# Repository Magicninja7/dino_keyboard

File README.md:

# Description
A keyboard with 84 keys, a ssd1306 mini-display, and 2 ec11 potentiometers. It has a unque look, with lots of extra keys for ex. undo, copy, paste, print, etc. You can also control the brightness and volume with the knobs (yes, i change the brightness that often).
Why? i literally thought: hmm, a keyboard would look nice on my desk. And highway happened, so i actually did it! 

### CAD render

### PCB

### diagram

# BOM
| item        | price   | quantity | total | link |
| ----------- | ------- | -------- | ----- | ---- |
| ssd1306     | 2$      | 1        | 2$    | https://pl.aliexpress.com/item/1005007755490093.html?spm=a2g0o.productlist.main.1.6c10EyamEyam6L&aem_p4p_detail=20250630235822166496048688330000078262&algo_pvid=038de64f-8493-4f19-a7da-75bfefd5f6e4&algo_exp_id=038de64f-8493-4f19-a7da-75bfefd5f6e4-0&pdp_ext_f=%7B%22order%22%3A%22867%22%2C%22eval%22%3A%221%22%7D&pdp_npi=4%40dis%21PLN%214.37%213.66%21%21%218.47%217.09%21%402103846917513531028413088edbc9%2112000046602990083%21sea%21PL%210%21ABX&curPageLogUid=qcVLLUaP9Bsu&utparam-url=scene%3Asearch%7Cquery_from%3A&search_p4p_id=20250630235822166496048688330000078262_1 |
| cherry mx switch | 33$ | 90 | 33$ | https://pl.aliexpress.com/item/1005007907313874.html?spm=a2g0o.productlist.main.1.6d43246478dk2s&aem_p4p_detail=202507010000501353885340096940000087764&algo_pvid=38e9dc26-609e-4778-bdfd-8964c1d5e858&algo_exp_id=38e9dc26-609e-4778-bdfd-8964c1d5e858-0&pdp_ext_f=%7B%22order%22%3A%22165%22%2C%22eval%22%3A%221%22%7D&pdp_npi=4%40dis%21PLN%2121.53%2117.95%21%21%215.83%214.86%21%40211b680e17513532500874294ef58c%2112000042798939807%21sea%21PL%210%21ABX&curPageLogUid=2yr5disCnjNM&utparam-url=scene%3Asearch%7Cquery_from%3A&search_p4p_id=202507010000501353885340096940000087764_1
| keycaps | 25$ | 125 | 25$ | https://www.ebay.com/itm/374554619019?var=643532147086&utm_source=chatgpt.com
| raspi pico | - | 2 | - | - |
| EC11 rotary encoder | 1$ | 2 | 2$ | https://kamami.pl/enkodery/1191644-modul-encoder-impulsator-ec11-20-impulsow-z-przyciskiem-rotary-enkoder-5906623487332.html?gQT=1
| PCB | 45$ | 1 | 45$ | n/d

total w/ customs & shipping = ~150$  (yay customs & shipping costs, how lovely)

Note: the places where i placed -, means i already have that part so i don't need to purchase it

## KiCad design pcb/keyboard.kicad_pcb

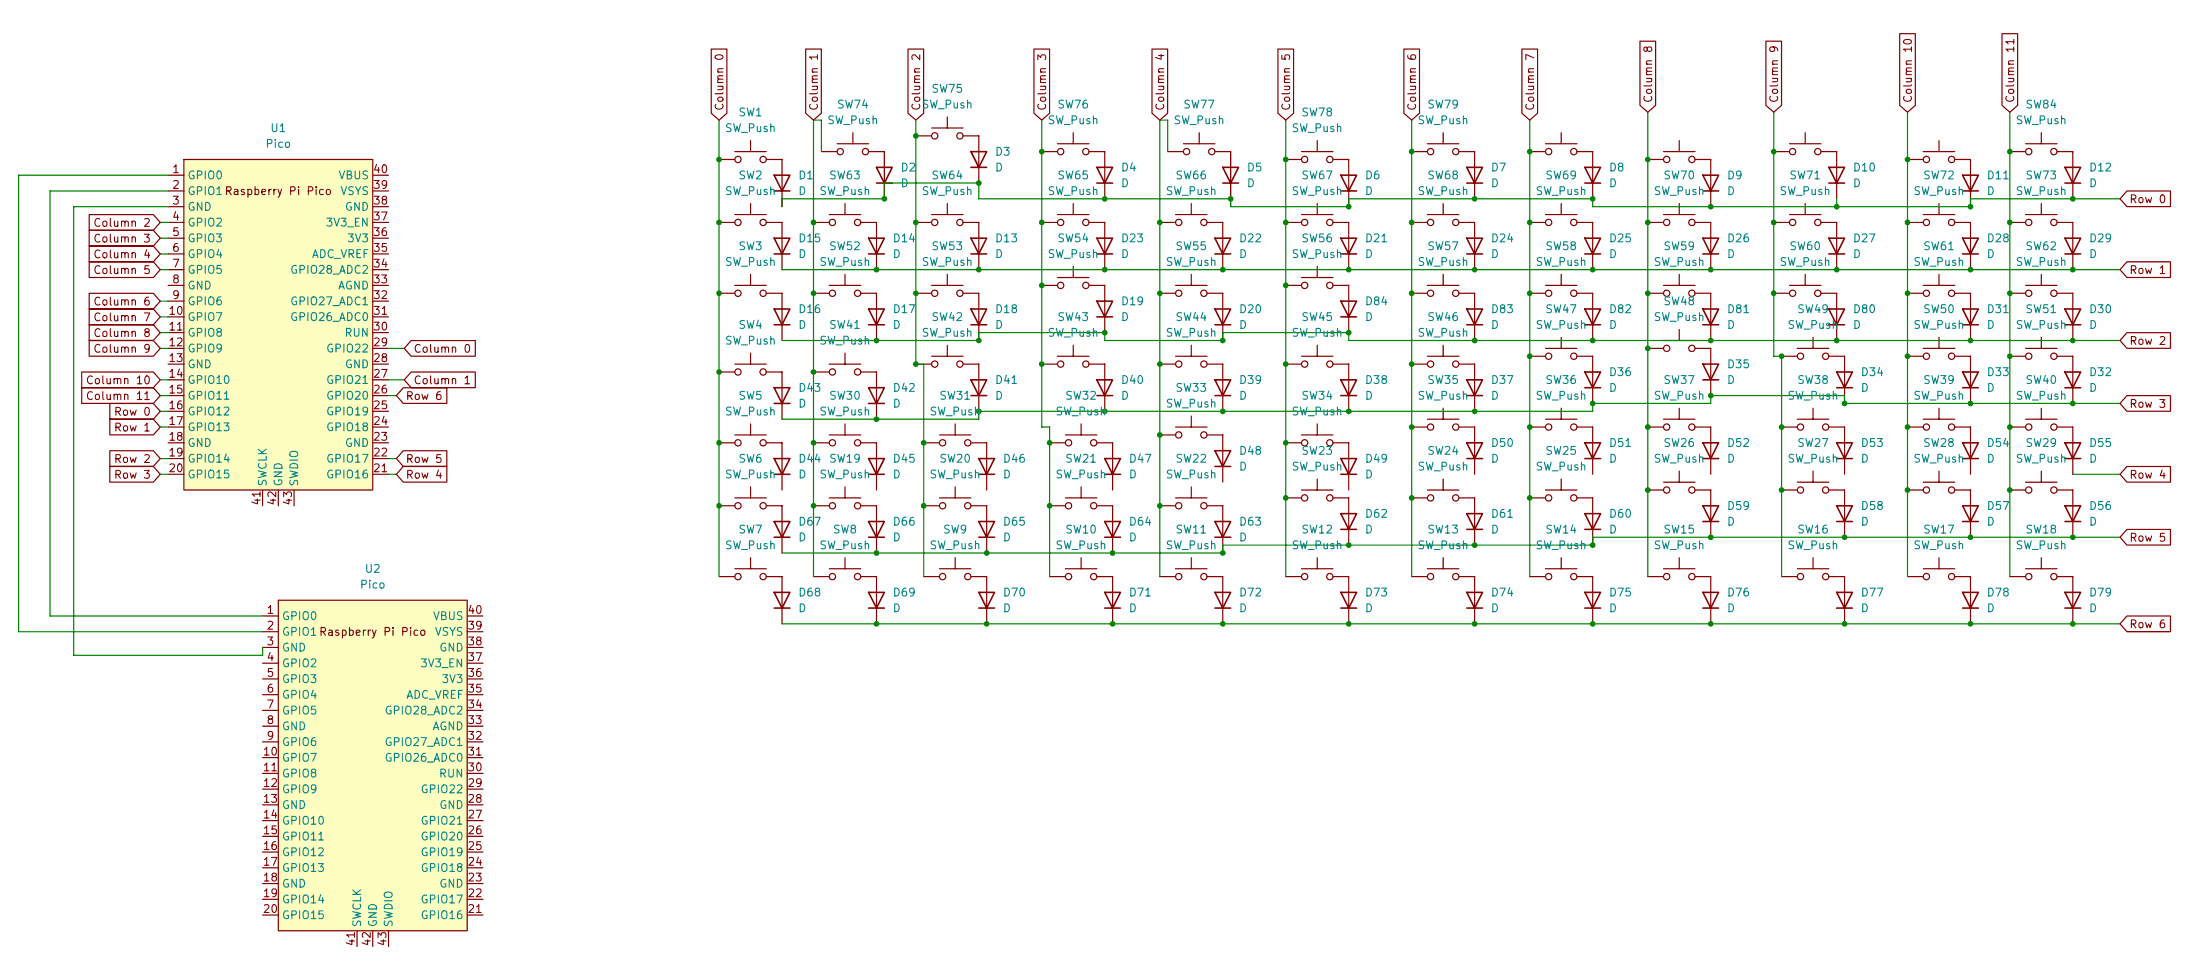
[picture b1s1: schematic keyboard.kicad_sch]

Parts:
D1, D2, D3, D4, D5, D6, D7, D8, D9, D10, D11, D12, D13, D14, D15, D16, D17, D18, D19, D20, D21, D22, D23, D24, D25, D26, D27, D28, D29, D30, D31, D32, D33, D34, D35, D36, D37, D38, D39, D40, D41, D42, D43, D44, D45, D46, D47, D48, D49, D50, D51, D52, D53, D54, D55, D56, D57, D58, D59, D60, D61, D62, D63, D64, D65, D66, D67, D68, D69, D70, D71, D72, D73, D74, D75, D76, D77, D78, D79, D80, D81, D82, D83, D84: D; LED_0201_0603Metric
SW1, SW2, SW3, SW4, SW5, SW6, SW7, SW8, SW9, SW10, SW11, SW12, SW13, SW14, SW15, SW16, SW17, SW18, SW19, SW20, SW21, SW22, SW23, SW24, SW25, SW26, SW27, SW28, SW29, SW30, SW31, SW32, SW33, SW34, SW35, SW36, SW37, SW38, SW39, SW40, SW41, SW42, SW43, SW44, SW45, SW46, SW47, SW48, SW49, SW52, SW53, SW54, SW55, SW56, SW57, SW58, SW60, SW61, SW62, SW63, SW64, SW65, SW66, SW67, SW68, SW69, SW70, SW71, SW72, SW73, SW74, SW75, SW76, SW77, SW78, SW79, SW80, SW81, SW82, SW83, SW84: SW_Push; SW_Cherry_MX_1.00u_PCB
SW50, SW51: SW_Push; SW_Cherry_MX_1.75u_PCB
SW59: SW_Push; SW_Cherry_MX_2.75u_PCB
U1, U2: Pico; RPi_Pico_SMD_TH

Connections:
Column 0: SW1.1, SW2.1, SW3.1, SW4.1, SW5.1, SW6.1, SW7.1, U1.29 (GPIO22)
Column 1: SW8.1, SW19.1, SW30.1, SW41.1, SW52.1, SW63.1, SW74.1, U1.27 (GPIO21)
Column 2: SW9.1, SW20.1, SW31.1, SW42.1, SW53.1, SW64.1, SW75.1, U1.4 (GPIO2)
Column 3: SW10.1, SW21.1, SW32.1, SW43.1, SW54.1, SW65.1, SW76.1, U1.5 (GPIO3)
Column 4: SW11.1, SW22.1, SW33.1, SW44.1, SW55.1, SW66.1, SW77.1, U1.6 (GPIO4)
Column 5: SW12.1, SW23.1, SW34.1, SW45.1, SW56.1, SW67.1, SW78.1, U1.7 (GPIO5)
Column 6: SW13.1, SW24.1, SW35.1, SW46.1, SW57.1, SW68.1, SW79.1, U1.9 (GPIO6)
Column 7: SW14.1, SW25.1, SW36.1, SW47.1, SW58.1, SW69.1, SW80.1, U1.10 (GPIO7)
Column 8: SW15.1, SW26.1, SW37.1, SW48.1, SW59.1, SW70.1, SW81.1, U1.11 (GPIO8)
Column 9: SW16.1, SW27.1, SW38.1, SW49.1, SW60.1, SW71.1, SW82.1, U1.12 (GPIO9)
Column 10: SW17.1, SW28.1, SW39.1, SW50.1, SW61.1, SW72.1, SW83.1, U1.14 (GPIO10)
Column 11: SW18.1, SW29.1, SW40.1, SW51.1, SW62.1, SW73.1, SW84.1, U1.15 (GPIO11)
unnamed: D1.2 (A), SW1.2
unnamed: D2.2 (A), SW74.2
unnamed: D3.2 (A), SW75.2
unnamed: D4.2 (A), SW76.2
unnamed: D5.2 (A), SW77.2
unnamed: D6.2 (A), SW78.2
unnamed: D7.2 (A), SW79.2
unnamed: D8.2 (A), SW80.2
unnamed: D9.2 (A), SW81.2
unnamed: D10.2 (A), SW82.2
unnamed: D11.2 (A), SW83.2
unnamed: D12.2 (A), SW84.2
unnamed: D13.2 (A), SW64.2
unnamed: D14.2 (A), SW63.2
unnamed: D15.2 (A), SW2.2
unnamed: D16.2 (A), SW3.2
unnamed: D17.2 (A), SW52.2
unnamed: D18.2 (A), SW53.2
unnamed: D19.2 (A), SW54.2
unnamed: D20.2 (A), SW55.2
unnamed: D21.2 (A), SW67.2
unnamed: D22.2 (A), SW66.2
unnamed: D23.2 (A), SW65.2
unnamed: D24.2 (A), SW68.2
unnamed: D25.2 (A), SW69.2
unnamed: D26.2 (A), SW70.2
unnamed: D27.2 (A), SW71.2
unnamed: D28.2 (A), SW72.2
unnamed: D29.2 (A), SW73.2
unnamed: D30.2 (A), SW62.2
unnamed: D31.2 (A), SW61.2
unnamed: D32.2 (A), SW51.2
unnamed: D33.2 (A), SW50.2
unnamed: D34.2 (A), SW49.2
unnamed: D35.2 (A), SW48.2
unnamed: D36.2 (A), SW47.2
unnamed: D37.2 (A), SW46.2
unnamed: D38.2 (A), SW45.2
unnamed: D39.2 (A), SW44.2
unnamed: D40.2 (A), SW43.2
unnamed: D41.2 (A), SW42.2
unnamed: D42.2 (A), SW41.2
unnamed: D43.2 (A), SW4.2
unnamed: D44.2 (A), SW5.2
unnamed: D45.2 (A), SW30.2
unnamed: D46.2 (A), SW31.2
unnamed: D47.2 (A), SW32.2
unnamed: D48.2 (A), SW33.2
unnamed: D49.2 (A), SW34.2
unnamed: D50.2 (A), SW35.2
unnamed: D51.2 (A), SW36.2
unnamed: D52.2 (A), SW37.2
unnamed: D53.2 (A), SW38.2
unnamed: D54.2 (A), SW39.2
unnamed: D55.2 (A), SW40.2
unnamed: D56.2 (A), SW29.2
unnamed: D57.2 (A), SW28.2
unnamed: D58.2 (A), SW27.2
unnamed: D59.2 (A), SW26.2
unnamed: D60.2 (A), SW25.2
unnamed: D61.2 (A), SW24.2
unnamed: D62.2 (A), SW23.2
unnamed: D63.2 (A), SW22.2
unnamed: D64.2 (A), SW21.2
unnamed: D65.2 (A), SW20.2
unnamed: D66.2 (A), SW19.2
unnamed: D67.2 (A), SW6.2
unnamed: D68.2 (A), SW7.2
unnamed: D69.2 (A), SW8.2
unnamed: D70.2 (A), SW9.2
unnamed: D71.2 (A), SW10.2
unnamed: D72.2 (A), SW11.2
unnamed: D73.2 (A), SW12.2
unnamed: D74.2 (A), SW13.2
unnamed: D75.2 (A), SW14.2
unnamed: D76.2 (A), SW15.2
unnamed: D77.2 (A), SW16.2
unnamed: D78.2 (A), SW17.2
unnamed: D79.2 (A), SW18.2
unnamed: D80.2 (A), SW60.2
unnamed: D81.2 (A), SW59.2
unnamed: D82.2 (A), SW58.2
unnamed: D83.2 (A), SW57.2
unnamed: D84.2 (A), SW56.2
unnamed: U1.3 (GND), U2.3 (GND)
unnamed: U1.1 (GPIO0), U2.2 (GPIO1)
unnamed: U1.2 (GPIO1), U2.1 (GPIO0)
Row 0: D1.1 (K), D2.1 (K), D3.1 (K), D4.1 (K), D5.1 (K), D6.1 (K), D7.1 (K), D8.1 (K), D9.1 (K), D10.1 (K), D11.1 (K), D12.1 (K), U1.16 (GPIO12)
Row 1: D13.1 (K), D14.1 (K), D15.1 (K), D21.1 (K), D22.1 (K), D23.1 (K), D24.1 (K), D25.1 (K), D26.1 (K), D27.1 (K), D28.1 (K), D29.1 (K), U1.17 (GPIO13)
Row 2: D16.1 (K), D17.1 (K), D18.1 (K), D19.1 (K), D20.1 (K), D30.1 (K), D31.1 (K), D80.1 (K), D81.1 (K), D82.1 (K), D83.1 (K), D84.1 (K), U1.19 (GPIO14)
Row 3: D32.1 (K), D33.1 (K), D34.1 (K), D35.1 (K), D36.1 (K), D37.1 (K), D38.1 (K), D39.1 (K), D40.1 (K), D41.1 (K), D42.1 (K), D43.1 (K), U1.20 (GPIO15)
Row 4: D55.1 (K), U1.21 (GPIO16)
Row 5: D56.1 (K), D57.1 (K), D58.1 (K), D59.1 (K), D60.1 (K), D61.1 (K), D62.1 (K), D63.1 (K), D64.1 (K), D65.1 (K), D66.1 (K), D67.1 (K), U1.22 (GPIO17)
Row 6: D68.1 (K), D69.1 (K), D70.1 (K), D71.1 (K), D72.1 (K), D73.1 (K), D74.1 (K), D75.1 (K), D76.1 (K), D77.1 (K), D78.1 (K), D79.1 (K), U1.26 (GPIO20)

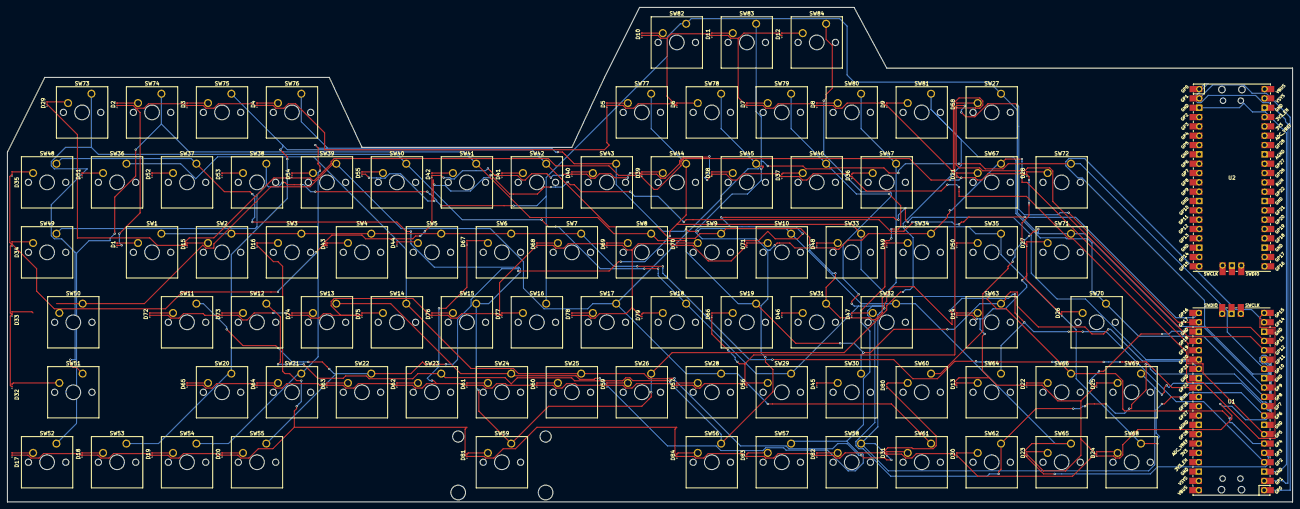
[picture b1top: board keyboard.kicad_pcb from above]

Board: 2 copper layers, 349.9 x 134.6 mm, 170 parts (0 on the bottom side), 106 nets.

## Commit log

2025-06-28 Rename devlog.md to journal.md
2025-07-01 Rename plate-2025-05-24T16_50_25.808Z.dxf to cad/plate-2025-05-24T16_50_25.808Z.dxf
2025-07-01 Rename keyboard.step to cad/keyboard.step
2025-07-01 Rename SSD1306_OLED_Display(128x64).step to cad/SSD1306_OLED_Display(128x64).step
2025-07-01 Rename EC11 Rotary Encoder Dode Switch-15mm .STEP to cad/EC11 Rotary Encoder Dode Switch-15mm .STEP
2025-07-01 Rename keymap.c to firmware/keymap.c
